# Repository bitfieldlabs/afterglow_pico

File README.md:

# Afterglow Pico
The afterglow pico is the newest and tiniest addition to the afterglow family.

It operates differently from the other boards as it is hooked directly into the WPC bus. The underlying concept remains the same though. The original lamp matrix is resampled at 4kHz and PWM is used to add a nice afterglow to the LEDs in your pinball machine.

## Disclaimer

| :boom: WARNING  :boom:            |
|:---------------------------|
| **Messing with your pinball machine's data bus is risky!** |
| *The AG pico is an experiment, for stable afterglow please<br>use the standard afterglow boards.* |

Afterglow is distributed in the hope that it will be useful but WITHOUT ANY WARRANTY; without even the implied warranty of
MERCHANTABILITY or FITNESS FOR A PARTICULAR PURPOSE.  See the GNU Lesser General Public License for more details.

## Concept
The concept is quite simple:
* The lamp matrix status is sampled directly from the WPC bus by the Raspberry Pi Pico
* All non lamp related address lines (solenoids etc.) are logically combined (AND) to monitor bus activity
* All non lamp related bus events are directly routed through a multiplexer to the output. Only the lamp events are filtered out. This ensures that original bus events always take precedence over the Pi signals and that no original events are lost.
* The Pi Pico interleaves the upsampled 4kHz PWM lamp matrix events into the bus through the multiplexer

## Compiling the Raspberry Pi Pico code

The [pi_pico_code folder](https://github.com/bitfieldlabs/afterglow_pico/tree/master/pi_pico_code) contains a [platformio](https://platformio.org/) project which can be compiled using [Visual Studio Code](https://code.visualstudio.com/). It requires the [wizio-pico](https://github.com/Wiz-IO/wizio-pico) platform extension.

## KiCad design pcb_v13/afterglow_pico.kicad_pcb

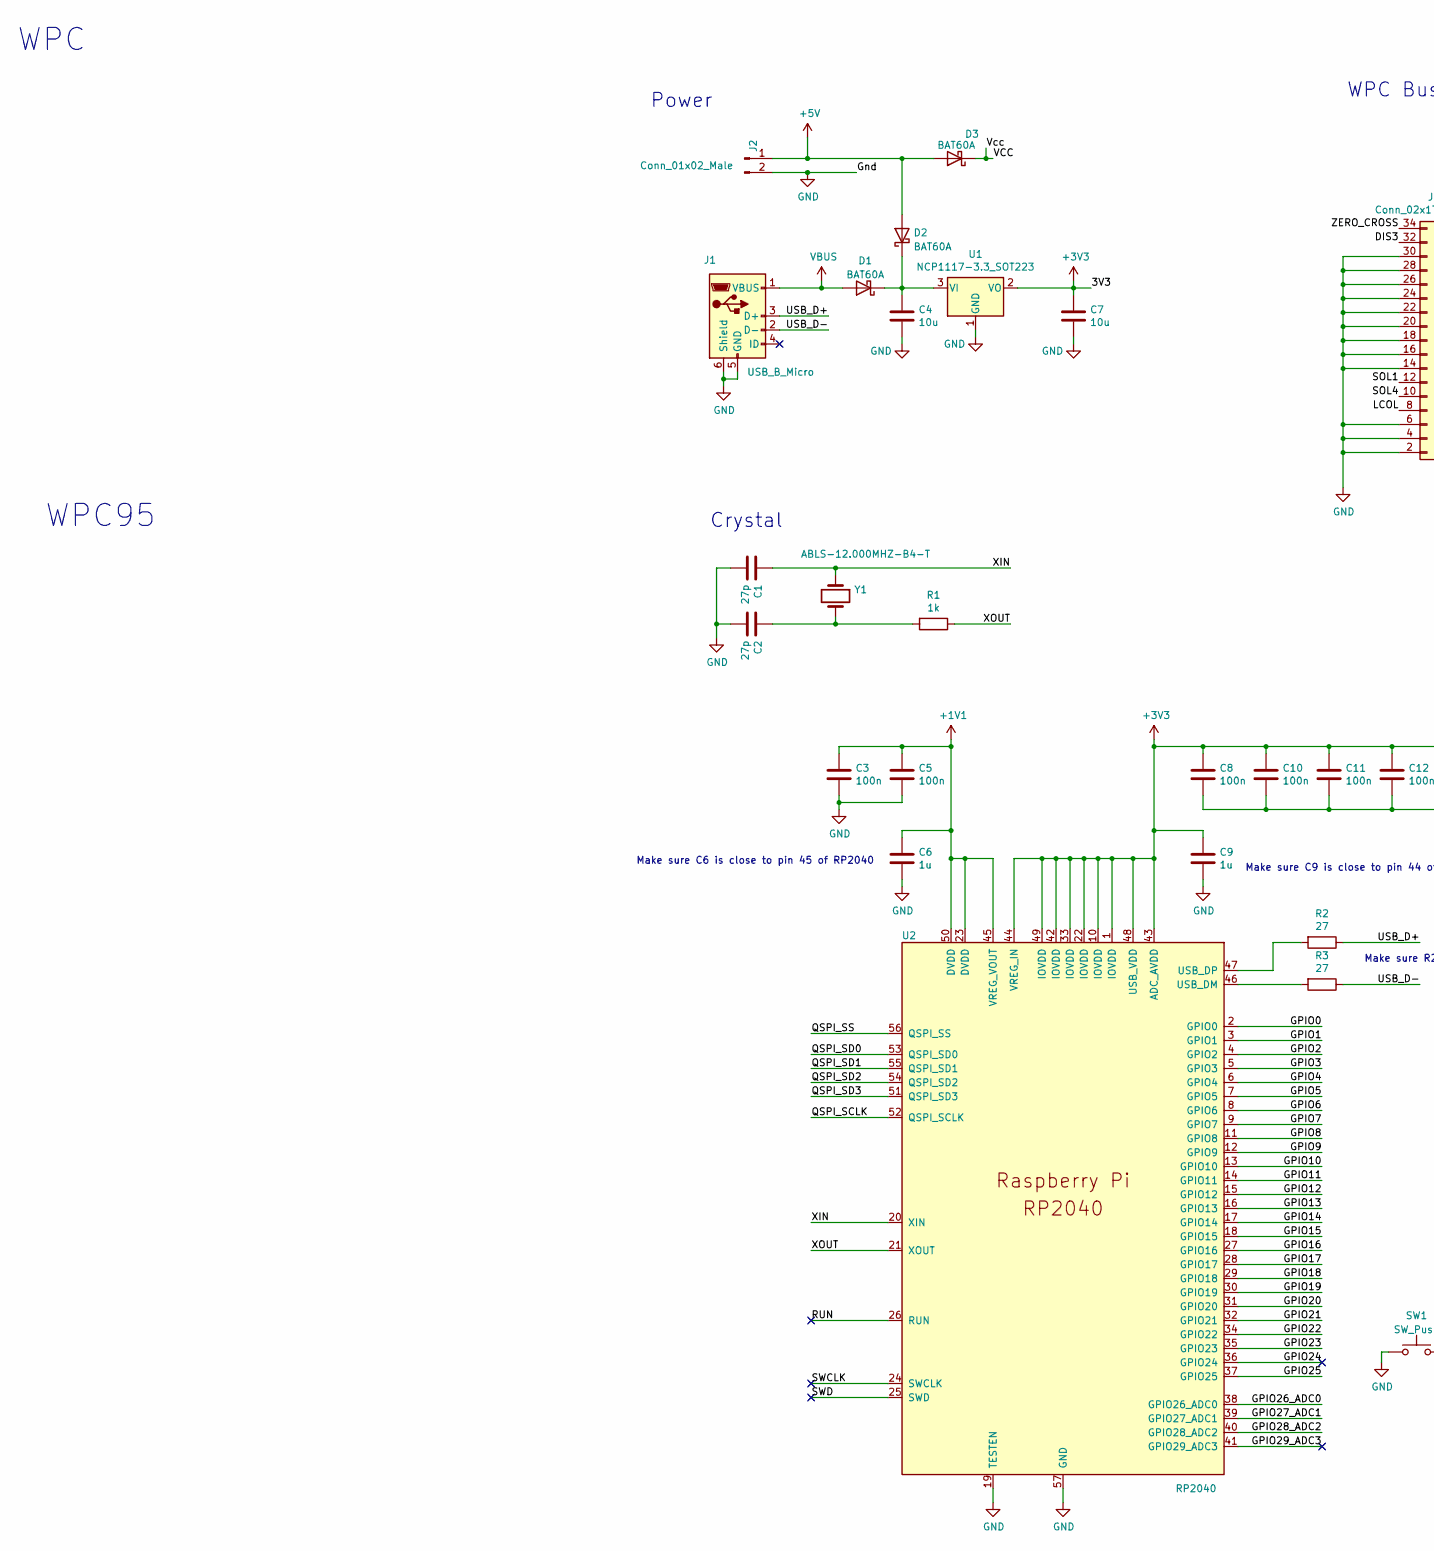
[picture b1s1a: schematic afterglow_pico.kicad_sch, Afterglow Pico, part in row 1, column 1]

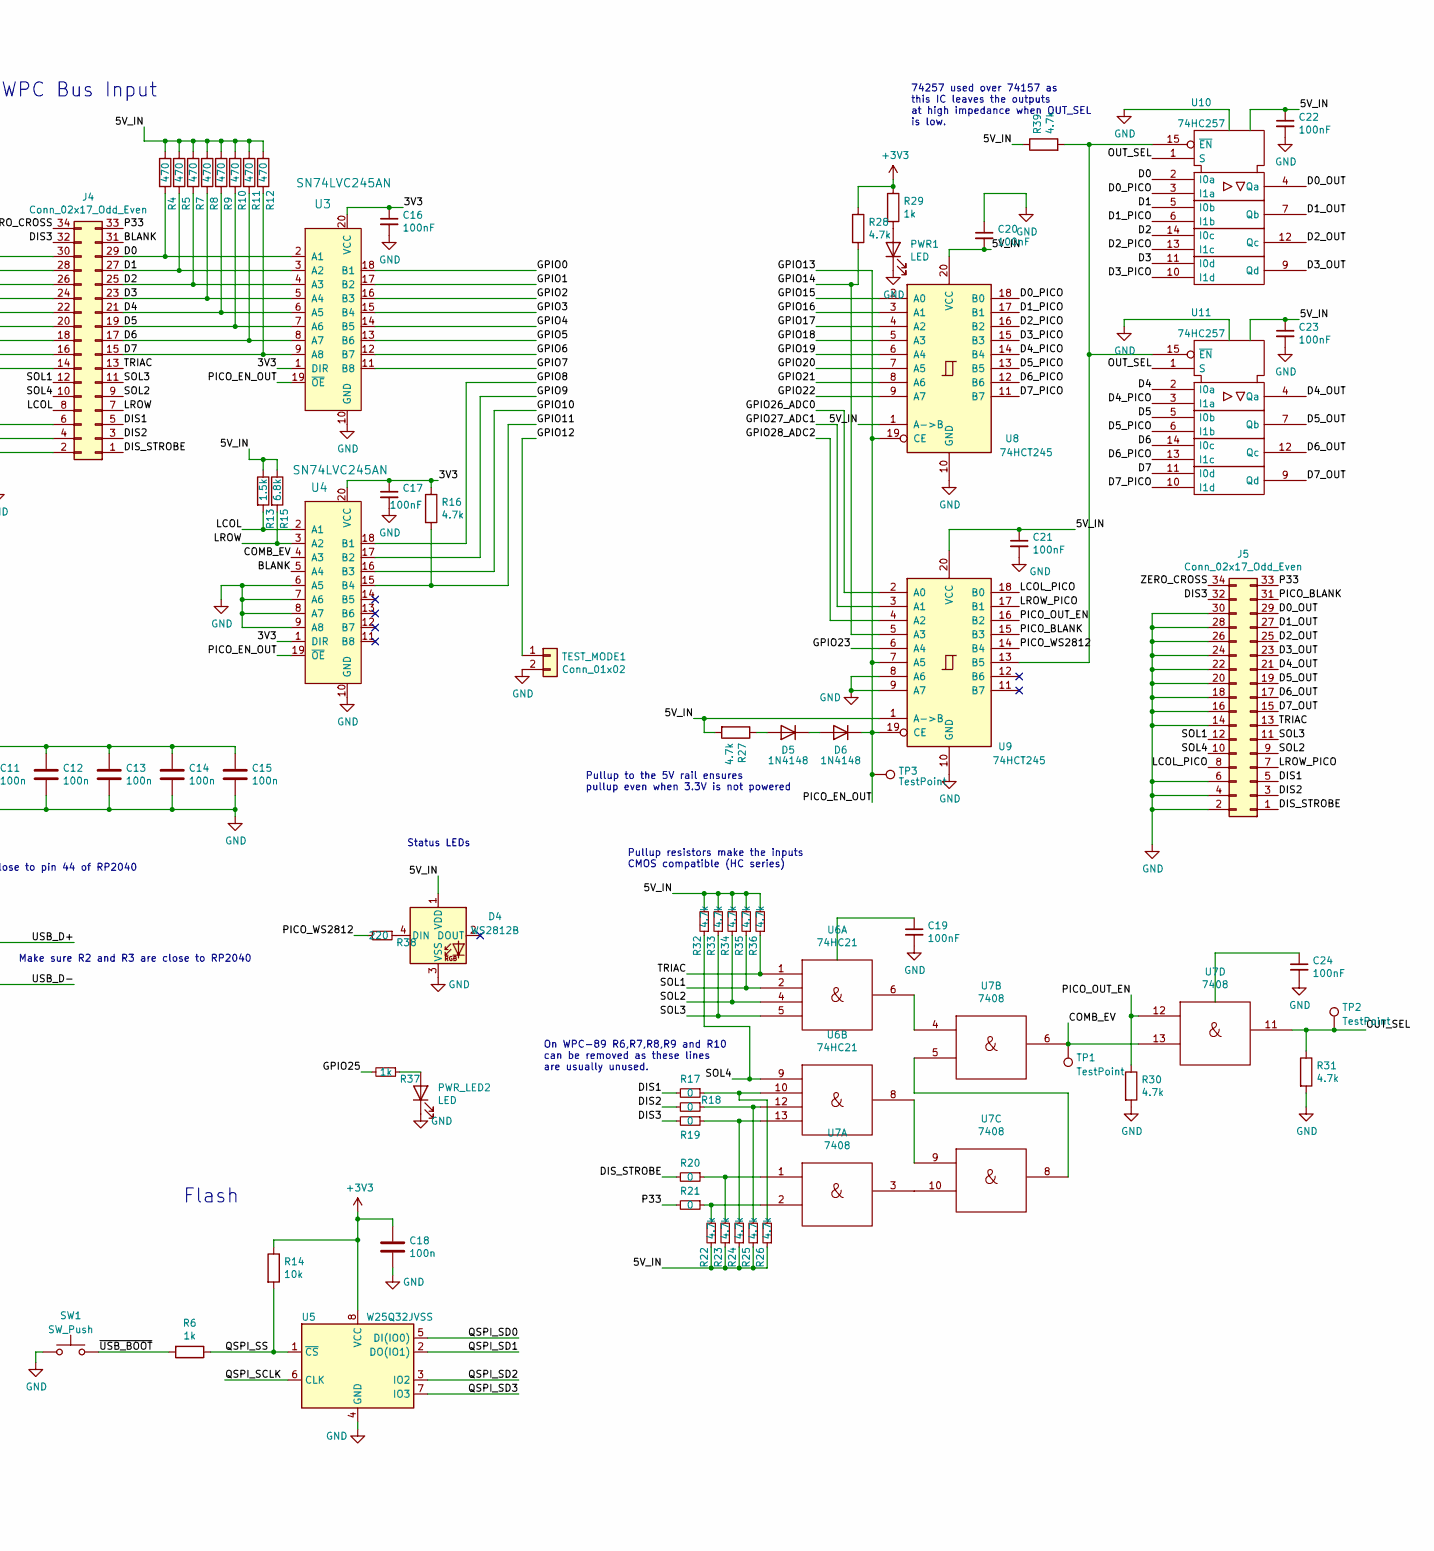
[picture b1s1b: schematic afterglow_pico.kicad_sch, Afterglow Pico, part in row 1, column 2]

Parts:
C1, C2: 27p; C_0402_1005Metric; JLCPCB C107002
C3, C5, C8, C10, C11, C12, C13, C14, C15, C18: 100n; C_0402_1005Metric; JLCPCB C131394
C4, C7: 10u; C_0805_2012Metric; JLCPCB C89189
C6, C9: 1u; C_0402_1005Metric; JLCPCB C326568
C16, C17, C19, C20, C21, C22, C23, C24: 100nF; C_0402_1005Metric; JLCPCB C131394
D1, D2, D3: BAT60A; D_SOD-323; JLCPCB C520634
D4: WS2812B; LED_WS2812B_PLCC4_5.0x5.0mm_P3.2mm; JLCPCB C2761795
D5, D6: 1N4148; D_SOD-523; JLCPCB C2961218
J1: USB_B_Micro; USB_Micro-B_Molex-105017-0001; JLCPCB C505111
J2: Conn_01x02_Male; Molex_KK-254_AE-6410-02A_1x02_P2.54mm_Vertical
J4: Conn_02x17_Odd_Even; PinHeader_2x17_P2.54mm_Vertical
J5: Conn_02x17_Odd_Even; PinHeader_2x17_P2.54mm_Vertical; JLCPCB C2894978
PWR1: LED; LED_0402_1005Metric; JLCPCB C434449
PWR_LED2: LED; LED_0402_1005Metric; JLCPCB C130719
R1, R6, R29, R37: 1k; R_0402_1005Metric; JLCPCB C106235
R2, R3: 27; R_0402_1005Metric; JLCPCB C137890
R4, R5, R7, R8, R9, R10, R11, R12: 470; R_0402_1005Metric; JLCPCB C114877
R13: 1.5k; R_0402_1005Metric; JLCPCB C114759
R14: 10k; R_0402_1005Metric; JLCPCB C60489
R15: 6.8k; R_0402_1005Metric; JLCPCB C137847
R16, R22, R23, R24, R25, R26, R27, R28, R30, R31, R32, R33, R34, R35, R36, R39: 4.7k; R_0402_1005Metric; JLCPCB C105871
R17, R18, R20, R21: 0; R_0402_1005Metric
R19: 0; R_0402_1005Metric; JLCPCB C138289
R38: 220; R_0402_1005Metric; JLCPCB C227335
SW1: SW_Push; SW_SPST_B3U-1000P; JLCPCB C231329
TEST_MODE1: Conn_01x02; PinHeader_1x02_P2.54mm_Vertical; JLCPCB C124375
TP1, TP2, TP3: TestPoint; TestPoint_Pad_D1.5mm
U1: NCP1117-3.3_SOT223; SOT-223-3_TabPin2; JLCPCB C26537
U2: RP2040; RP2040-QFN-56; JLCPCB C2040
U3, U4: SN74LVC245AN; TSSOP-20_4.4x6.5mm_P0.65mm; MPN SN74LVC245AN; Digi-Key_PN 296-8503-5-ND
U5: W25Q32JVSS; SOIC-8_5.23x5.23mm_P1.27mm; JLCPCB C82344
U6: 74HC21; SOIC-14_3.9x8.7mm_P1.27mm; JLCPCB C75398
U7: 7408; SOIC-14_3.9x8.7mm_P1.27mm; JLCPCB C5593
U8, U9: 74HCT245; TSSOP-20_4.4x6.5mm_P0.65mm; JLCPCB C6779
U10, U11: 74HC257; TSSOP-16_4.4x5mm_P0.65mm; JLCPCB C7646
Y1: ABLS-12.000MHZ-B4-T; Crystal_SMD_HC49-US; JLCPCB C390753

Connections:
+1V1: C3.1, C5.1, C6.1, U2.23 (DVDD), U2.45 (VREG_VOUT), U2.50 (DVDD)
+3V3: C7.1, C8.1, C9.1, C10.1, C11.1, C12.1, C13.1, C14.1, C15.1, C16.1, C17.1, C18.1, R14.1, R16.1, R28.1, R29.1, U1.2 (VO), U2.1 (IOVDD), U2.10 (IOVDD), U2.22 (IOVDD), U2.33 (IOVDD), U2.42 (IOVDD), U2.43 (ADC_AVDD), U2.44 (VREG_IN), U2.48 (USB_VDD), U2.49 (IOVDD), U3.1 (DIR), U3.20 (VCC), U4.1 (DIR), U4.20 (VCC), U5.8 (VCC)
+5V: D2.2 (A), D3.2 (A), J2.1; also elsewhere on the board
/BLANK: J4.31, U4.5 (A4)
/COMB_EV: TP1.1, U4.4 (A3), U7.6, U7.13
/D0: J4.29, R4.2, U3.2 (A1), U10.2 (I0a)
/D0_OUT: J5.29, U10.4 (Qa)
/D0_PICO: U8.18 (B0), U10.3 (I1a)
/D1: J4.27, R5.2, U3.3 (A2), U10.5 (I0b)
/D1_OUT: J5.27, U10.7 (Qb)
/D1_PICO: U8.17 (B1), U10.6 (I1b)
/D2: J4.25, R7.2, U3.4 (A3), U10.14 (I0c)
/D2_OUT: J5.25, U10.12 (Qc)
/D2_PICO: U8.16 (B2), U10.13 (I1c)
/D3: J4.23, R8.2, U3.5 (A4), U10.11 (I0d)
/D3_OUT: J5.23, U10.9 (Qd)
/D3_PICO: U8.15 (B3), U10.10 (I1d)
/D4: J4.21, R9.2, U3.6 (A5), U11.2 (I0a)
/D4_OUT: J5.21, U11.4 (Qa)
/D4_PICO: U8.14 (B4), U11.3 (I1a)
/D5: J4.19, R10.2, U3.7 (A6), U11.5 (I0b)
/D5_OUT: J5.19, U11.7 (Qb)
/D5_PICO: U8.13 (B5), U11.6 (I1b)
/D6: J4.17, R11.2, U3.8 (A7), U11.14 (I0c)
/D6_OUT: J5.17, U11.12 (Qc)
/D6_PICO: U8.12 (B6), U11.13 (I1c)
/D7: J4.15, R12.2, U3.9 (A8), U11.11 (I0d)
/D7_OUT: J5.15, U11.9 (Qd)
/D7_PICO: U8.11 (B7), U11.10 (I1d)
/DIS1: J4.5, J5.5, R17.2
/DIS2: J4.3, J5.3, R18.2
/DIS3: J4.32, J5.32, R19.2
/DIS_STROBE: J4.1, J5.1, R20.2
/GPIO0: U2.2 (GPIO0), U3.18 (B1)
/GPIO1: U2.3 (GPIO1), U3.17 (B2)
/GPIO2: U2.4 (GPIO2), U3.16 (B3)
/GPIO3: U2.5 (GPIO3), U3.15 (B4)
/GPIO4: U2.6 (GPIO4), U3.14 (B5)
/GPIO5: U2.7 (GPIO5), U3.13 (B6)
/GPIO6: U2.8 (GPIO6), U3.12 (B7)
/GPIO7: U2.9 (GPIO7), U3.11 (B8)
/GPIO8: U2.11 (GPIO8), U4.18 (B1)
/GPIO9: U2.12 (GPIO9), U4.17 (B2)
/GPIO10: U2.13 (GPIO10), U4.16 (B3)
/GPIO11: R16.2, U2.14 (GPIO11), U4.15 (B4)
/GPIO12: TEST_MODE1.1, U2.15 (GPIO12); also elsewhere on the board
/GPIO13: D6.1 (K), TP3.1, U2.16 (GPIO13), U3.19 (~OE), U4.19 (~OE), U8.19 (CE), U9.7 (A5), U9.19 (CE)
/GPIO14: R28.2, U2.17 (GPIO14), U9.5 (A3)
/GPIO15: U2.18 (GPIO15), U8.2 (A0)
/GPIO16: U2.27 (GPIO16), U8.3 (A1)
/GPIO17: U2.28 (GPIO17), U8.4 (A2)
/GPIO18: U2.29 (GPIO18), U8.5 (A3)
/GPIO19: U2.30 (GPIO19), U8.6 (A4)
/GPIO20: U2.31 (GPIO20), U8.7 (A5)
/GPIO21: U2.32 (GPIO21), U8.8 (A6)
/GPIO22: U2.34 (GPIO22), U8.9 (A7)
/GPIO23: U2.35 (GPIO23), U9.6 (A4)
/GPIO24: U2.36 (GPIO24)
/GPIO25: R37.2, U2.37 (GPIO25)
/GPIO26_ADC0: U2.38 (GPIO26_ADC0), U9.2 (A0)
/GPIO27_ADC1: U2.39 (GPIO27_ADC1), U9.3 (A1)
/GPIO28_ADC2: U2.40 (GPIO28_ADC2), U9.4 (A2)
/GPIO29_ADC3: U2.41 (GPIO29_ADC3)
/LCOL: J4.8, R13.2, U4.2 (A1)
/LCOL_PICO: J5.8, U9.18 (B0)
/LROW: J4.7, R15.2, U4.3 (A2)
/LROW_PICO: J5.7, U9.17 (B1)
/OUT_SEL: R31.1, TP2.1, U7.11, U10.1 (S), U11.1 (S)
/P33: J4.33, J5.33, R21.2
/PICO_BLANK: J5.31, U9.15 (B3)
/PICO_OUT_EN: R30.1, U7.12, U9.16 (B2)
/PICO_WS2812: R38.2, U9.14 (B4)
/QSPI_SCLK: U2.52 (QSPI_SCLK), U5.6 (CLK)
/QSPI_SD0: U2.53 (QSPI_SD0), U5.5 (DI(IO0))
/QSPI_SD1: U2.55 (QSPI_SD1), U5.2 (DO(IO1))
/QSPI_SD2: U2.54 (QSPI_SD2), U5.3 (IO2)
/QSPI_SD3: U2.51 (QSPI_SD3), U5.7 (IO3)
/QSPI_SS: R6.1, R14.2, U2.56 (QSPI_SS), U5.1 (~CS)
/RUN: U2.26 (RUN)
/SOL1: J4.12, J5.12, R35.1, U6.2
/SOL2: J4.9, J5.9, R34.1, U6.4
/SOL3: J4.11, J5.11, R33.1, U6.5
/SOL4: J4.10, J5.10, R32.1, U6.9
/SWCLK: U2.24 (SWCLK)
/SWD: U2.25 (SWD)
/TRIAC: J4.13, J5.13, R36.1, U6.1
/USB_D+: J1.3 (D+), R2.1
/USB_D-: J1.2 (D-), R3.1
/XIN: C1.1, U2.20 (XIN), Y1.1
/XOUT: R1.1, U2.21 (XOUT)
/ZERO_CROSS: J4.34, J5.34
/~USB_BOOT: R6.2, SW1.2
GND: C1.2, C2.2, C3.2, C4.2, C5.2, C6.2, C7.2, C8.2, C9.2, C10.2, C11.2, C12.2, C13.2, C14.2, C15.2, C16.2, C17.2, C18.2, C19.2, C20.1, C21.2, C22.2, C23.2, C24.2, D4.3 (VSS), J1.5 (GND), J1.6 (Shield), J2.2, J4.2, J4.4, J4.6, J4.14, J4.16, J4.18, J4.20, J4.22, J4.24, J4.26, J4.28, J4.30, J5.2, J5.4, J5.6, J5.14, J5.16, J5.18, J5.20, J5.22, J5.24, J5.26, J5.28, J5.30, PWR1.1 (K), PWR_LED2.1 (K), R30.2, R31.2, SW1.1, TEST_MODE1.2, U1.1 (GND), U2.19 (TESTEN), U2.57 (GND), U3.10 (GND), U4.6 (A5), U4.7 (A6), U4.8 (A7), U4.9 (A8), U4.10 (GND), U5.4 (GND), U6.7 (Gnd), U7.7 (Gnd), U8.10 (GND), U9.8 (A6), U9.9 (A7), U9.10 (GND), U10.8 (GND), U11.8 (GND); also elsewhere on the board
unnamed: C2.1, R1.2, Y1.2
unnamed: C4.1, D1.1 (K), D2.1 (K), U1.3 (VI)
unnamed: D4.4 (DIN), R38.1
unnamed: D5.2 (A), R27.1
unnamed: D5.1 (K), D6.2 (A)
unnamed 98: PWR1.2 (A), R29.2; also elsewhere on the board
unnamed: PWR_LED2.2 (A), R37.1
unnamed: R17.1, R26.2, U6.10
unnamed: R18.1, R25.2, U6.12
unnamed: R19.1, R24.2, U6.13
unnamed: R20.1, R23.2, U7.1
unnamed: R21.1, R22.2, U7.2
unnamed: R3.2, U2.46 (USB_DM)
unnamed: R2.2, U2.47 (USB_DP)
unnamed: U6.6, U7.4
unnamed: U6.8, U7.9
unnamed: U7.5, U7.8
unnamed: U7.3, U7.10
unnamed: R39.2, U9.13 (B5), U10.15 (~EN), U11.15 (~EN)
VBUS: D1.2 (A), J1.1 (VBUS)

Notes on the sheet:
WPC
Pullup to the 5V rail ensures pullup even when 3.3V is not powered
Status LEDs
Pullup resistors make the inputs CMOS compatible (HC series)
Make sure C9 is close to pin 44 of RP2040
Power
Crystal
74257 used over 74157 as this IC leaves the outputs at high impedance when OUT_SEL is low.
On WPC-89 R6,R7,R8,R9 and R10 can be removed as these lines are usually unused.
WPC Bus Input
WPC95
Make sure R2 and R3 are close to RP2040
Flash
Make sure C6 is close to pin 45 of RP2040

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
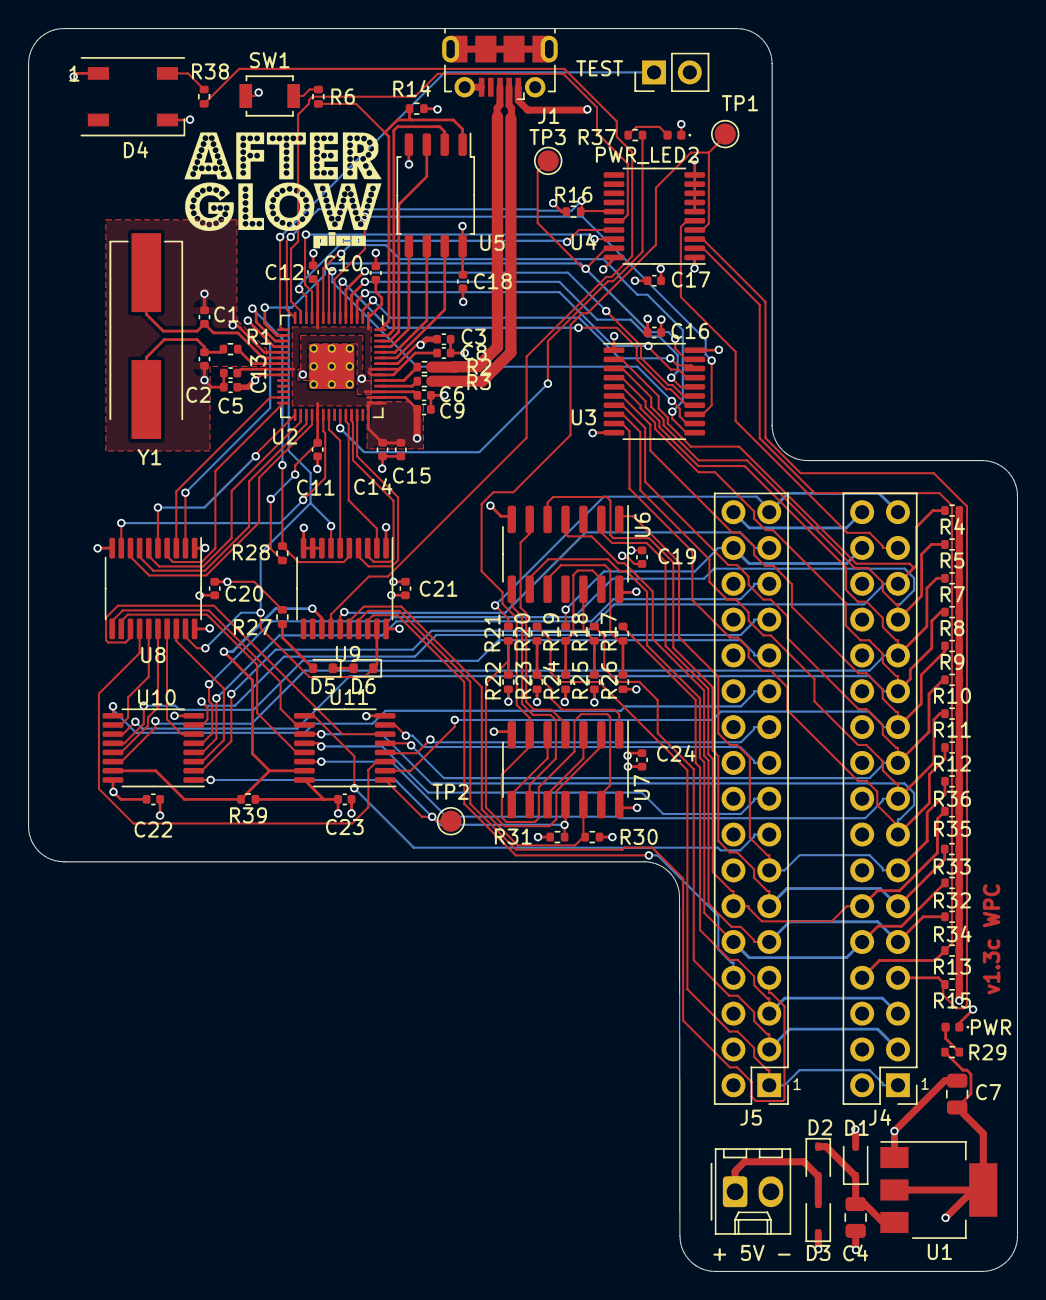
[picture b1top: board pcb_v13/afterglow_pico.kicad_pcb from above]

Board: 4 copper layers, 70.1 x 88.1 mm, 93 parts (0 on the bottom side), 109 nets.

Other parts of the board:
+ 5V -: Conn_01x02_Male; Molex_KK-254_AE-6410-02A_1x02_P2.54mm_Vertical
LOGO: LOGO; ag_pico_logo_2
PWR: LED; LED_0402_1005Metric
TEST: Conn_01x02; PinHeader_1x02_P2.54mm_Vertical

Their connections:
+5V: + 5V -.1; also elsewhere on the board
/GPIO12: TEST.1; also elsewhere on the board
GND: + 5V -.2, PWR.1 (K), TEST.2; also elsewhere on the board
unnamed 98: PWR.2 (A); also elsewhere on the board

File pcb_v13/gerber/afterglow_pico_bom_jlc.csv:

"Comment","Designator","Footprint","LCSC Part #"
"27p","C1,C2","C_0402_1005Metric","C107002"
"100n","C3,C5,C8,C10,C11,C12,C13,C14,C15,C18","C_0402_1005Metric","C131394"
"10u","C4,C7","C_0805_2012Metric","C89189"
"1u","C6,C9","C_0402_1005Metric","C326568"
"100nF","C16,C17,C19,C20,C21,C22,C23,C24","C_0402_1005Metric","C131394"
"BAT60A","D1,D2,D3","D_SOD-323","C520634"
"WS2812B","D4","LED_WS2812B_PLCC4_5.0x5.0mm_P3.2mm","C2761795"
"1N4148","D5,D6","D_SOD-523","C2961218"
"USB_B_Micro","J1","USB_Micro-B_Molex-105017-0001","C505111"
"Conn_02x17_Odd_Even","J5","PinHeader_2x17_P2.54mm_Vertical","C2894978"
"LED","PWR1","LED_0402_1005Metric","C434449"
"LED","PWR_LED2","LED_0402_1005Metric","C130719"
"1k","R1,R6,R29,R37","R_0402_1005Metric","C106235"
"27","R2,R3","R_0402_1005Metric","C137890"
"470","R4,R5,R7,R8,R9,R10,R11,R12","R_0402_1005Metric","C114877"
"1.5k","R13","R_0402_1005Metric","C114759"
"10k","R14","R_0402_1005Metric","C60489"
"6.8k","R15","R_0402_1005Metric","C137847"
"4.7k","R16,R22,R23,R24,R25,R26,R27,R28,R30,R31,R32,R33,R34,R35,R36,R39","R_0402_1005Metric","C105871"
"0","R19","R_0402_1005Metric","C138289"
"220","R38","R_0402_1005Metric","C227335"
"SW_Push","SW1","SW_SPST_B3U-1000P","C231329"
"Conn_01x02","TEST_MODE1","PinHeader_1x02_P2.54mm_Vertical","C124375"
"NCP1117-3.3_SOT223","U1","SOT-223-3_TabPin2","C26537"
"RP2040","U2","RP2040-QFN-56","C2040"
"SN74LVC245AN","U3,U4","TSSOP-20_4.4x6.5mm_P0.65mm","C6082"
"W25Q32JVSS","U5","SOIC-8_5.23x5.23mm_P1.27mm","C82344"
"74HC21","U6","SOIC-14_3.9x8.7mm_P1.27mm","C75398"
"7408","U7","SOIC-14_3.9x8.7mm_P1.27mm","C5593"
"74HCT245","U8,U9","TSSOP-20_4.4x6.5mm_P0.65mm","C6779"
"74HC257","U10,U11","TSSOP-16_4.4x5mm_P0.65mm","C7646"
"ABLS-12.000MHZ-B4-T","Y1","Crystal_SMD_HC49-US","C390753"

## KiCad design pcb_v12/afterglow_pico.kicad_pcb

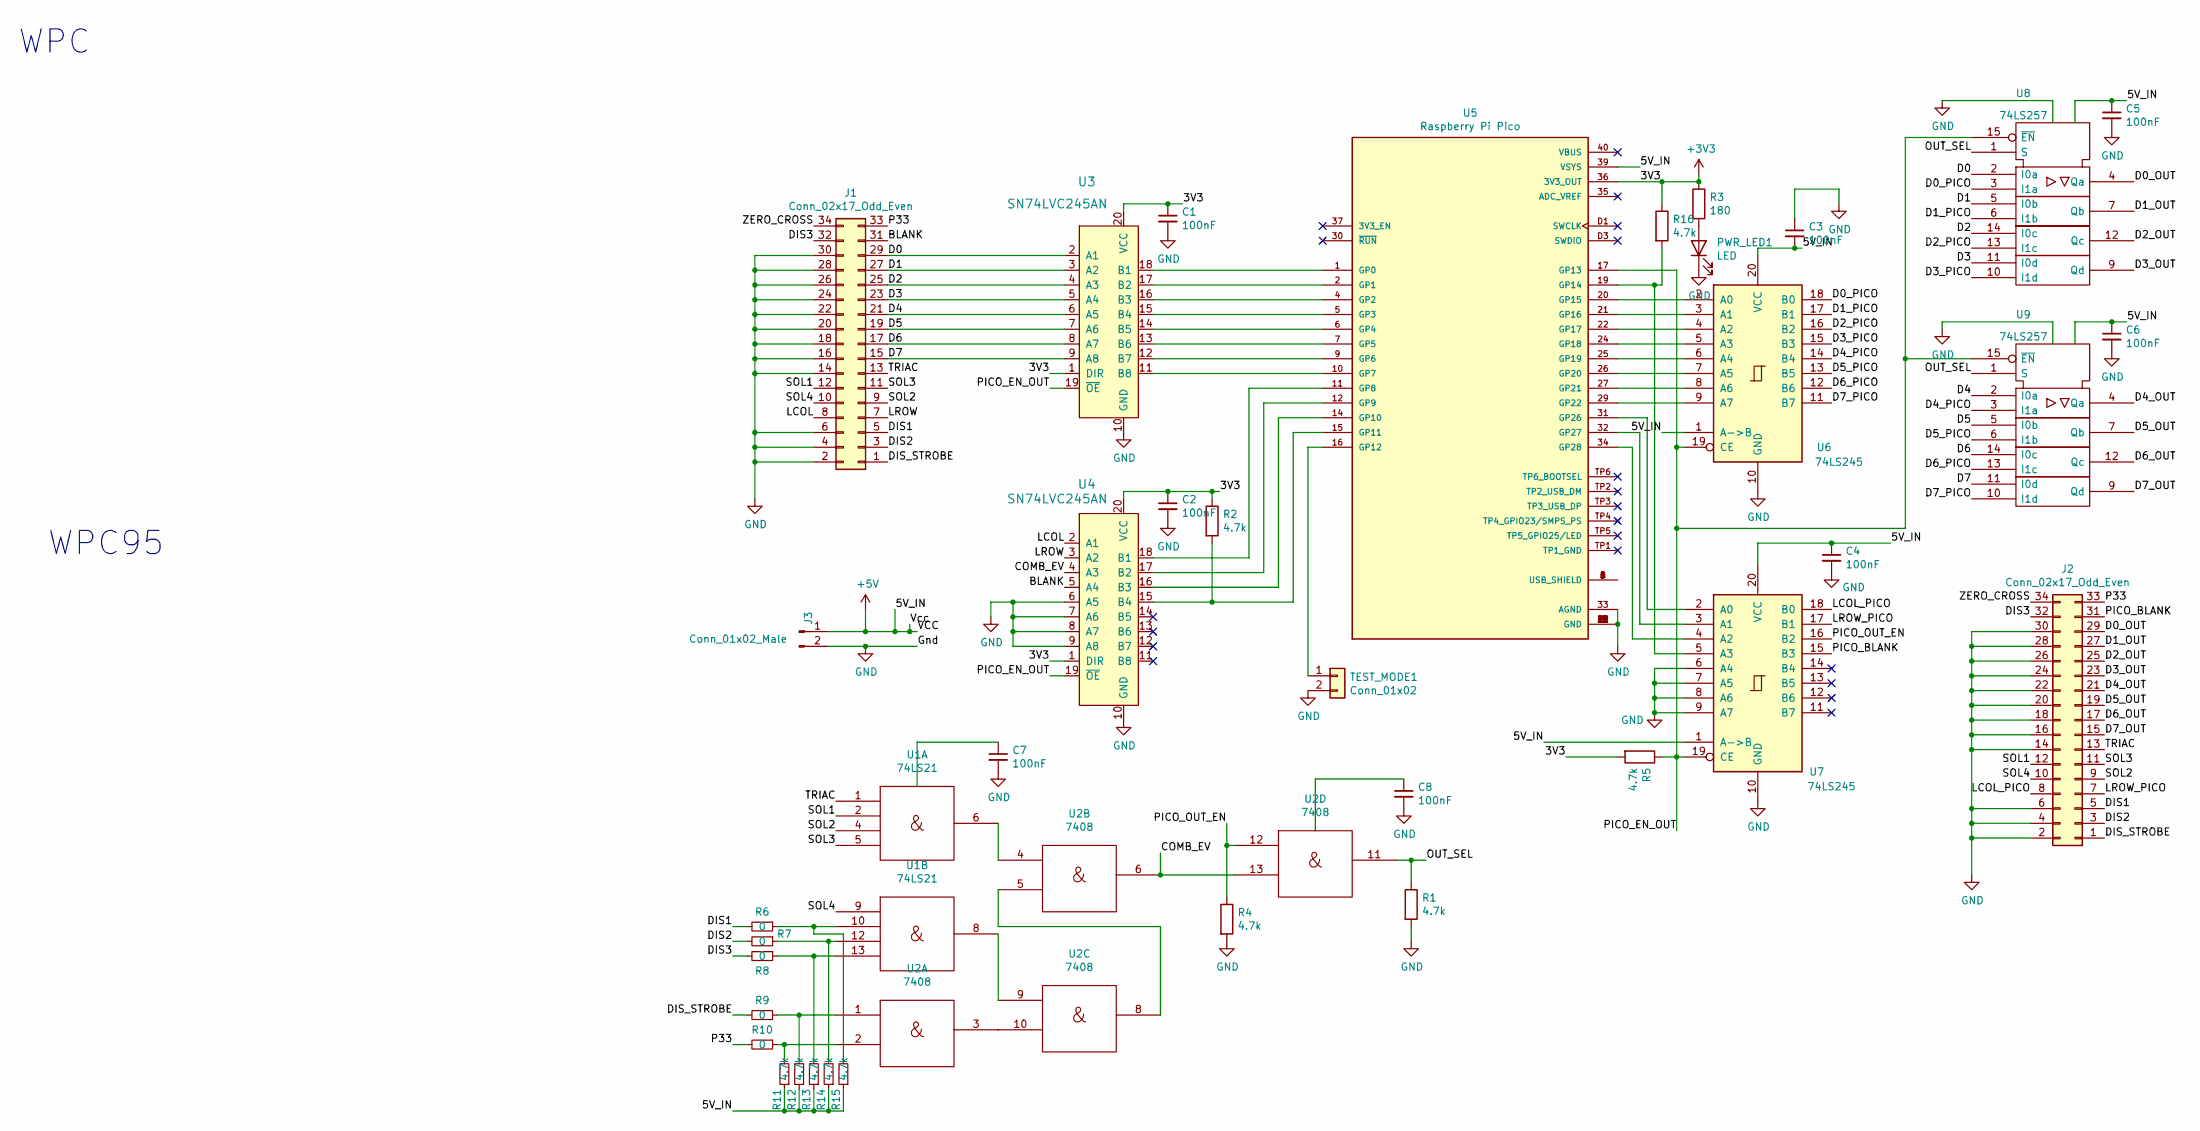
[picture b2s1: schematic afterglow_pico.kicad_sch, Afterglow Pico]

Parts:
C1, C2, C3, C4, C5, C6, C7, C8: 100nF; C_0805_HandSoldering; JLCPCB C396718
J1, J2: Conn_02x17_Odd_Even; Pin_Header_Straight_2x17_Pitch2.54mm
J3: Conn_01x02_Male; Molex_KK-6410-02_02x2.54mm_Straight
PWR_LED1: LED; LED_0805_HandSoldering; JLCPCB C434432
R1, R2, R4, R5, R11, R12, R13, R14, R15, R16: 4.7k; R_0805_HandSoldering; JLCPCB C17673
R3: 180; R_0805_HandSoldering; JLCPCB C25270
R6, R7, R8, R9, R10: 0; R_0805_HandSoldering; JLCPCB C17477
TEST_MODE1: Conn_01x02; Pin_Header_Straight_1x02_Pitch2.54mm
U1: 74LS21; SOIC-14_3.9x8.7mm_Pitch1.27mm; JLCPCB C2862597
U2: 7408; SOIC-14_3.9x8.7mm_Pitch1.27mm; JLCPCB C6802
U3, U4: SN74LVC245AN; SOIC-20W_7.5x12.8mm_Pitch1.27mm; MPN SN74LVC245AN; Digi-Key_PN 296-8503-5-ND
U5: Raspberry Pi Pico; MODULE_SC0915; PARTREV 1.6
U6, U7: 74LS245; SOIC-20W_7.5x12.8mm_Pitch1.27mm; JLCPCB C129580
U8, U9: 74LS257; SOP-16_4.4x10.4mm_Pitch1.27mm; JLCPCB C7754

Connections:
+3V3: C1.1, C2.1, R2.1, R3.1, R5.2, R16.1, U3.1 (DIR), U3.20 (VCC), U4.1 (DIR), U4.20 (VCC), U5.36 (3V3_OUT)
/BLANK: J1.31, U4.5 (A4)
/COMB_EV: U2.6, U2.13, U4.4 (A3)
/D0: J1.29, U3.2 (A1), U8.2 (I0a)
/D0_OUT: J2.29, U8.4 (Qa)
/D0_PICO: U6.18 (B0), U8.3 (I1a)
/D1: J1.27, U3.3 (A2), U8.5 (I0b)
/D1_OUT: J2.27, U8.7 (Qb)
/D1_PICO: U6.17 (B1), U8.6 (I1b)
/D2: J1.25, U3.4 (A3), U8.14 (I0c)
/D2_OUT: J2.25, U8.12 (Qc)
/D2_PICO: U6.16 (B2), U8.13 (I1c)
/D3: J1.23, U3.5 (A4), U8.11 (I0d)
/D3_OUT: J2.23, U8.9 (Qd)
/D3_PICO: U6.15 (B3), U8.10 (I1d)
/D4: J1.21, U3.6 (A5), U9.2 (I0a)
/D4_OUT: J2.21, U9.4 (Qa)
/D4_PICO: U6.14 (B4), U9.3 (I1a)
/D5: J1.19, U3.7 (A6), U9.5 (I0b)
/D5_OUT: J2.19, U9.7 (Qb)
/D5_PICO: U6.13 (B5), U9.6 (I1b)
/D6: J1.17, U3.8 (A7), U9.14 (I0c)
/D6_OUT: J2.17, U9.12 (Qc)
/D6_PICO: U6.12 (B6), U9.13 (I1c)
/D7: J1.15, U3.9 (A8), U9.11 (I0d)
/D7_OUT: J2.15, U9.9 (Qd)
/D7_PICO: U6.11 (B7), U9.10 (I1d)
/DIS1: J1.5, J2.5, R6.2
/DIS2: J1.3, J2.3, R7.2
/DIS3: J1.32, J2.32, R8.2
/DIS_STROBE: J1.1, J2.1, R9.2
/LCOL: J1.8, U4.2 (A1)
/LCOL_PICO: J2.8, U7.18 (B0)
/LROW: J1.7, U4.3 (A2)
/LROW_PICO: J2.7, U7.17 (B1)
/OUT_SEL: R1.1, U2.11, U8.1 (S), U9.1 (S)
/P33: J1.33, J2.33, R10.2
/PICO_BLANK: J2.31, U7.15 (B3)
/PICO_EN_OUT: R5.1, U3.19 (~OE), U4.19 (~OE), U5.17 (GP13), U6.19 (CE), U7.19 (CE), U8.15 (~EN), U9.15 (~EN)
/PICO_OUT_EN: R4.1, U2.12, U7.16 (B2)
/SOL1: J1.12, J2.12, U1.2
/SOL2: J1.9, J2.9, U1.4
/SOL3: J1.11, J2.11, U1.5
/SOL4: J1.10, J2.10, U1.9
/TRIAC: J1.13, J2.13, U1.1
/ZERO_CROSS: J1.34, J2.34
GND: C1.2, C2.2, C3.1, C4.2, C5.2, C6.2, C7.2, C8.2, J1.2, J1.4, J1.6, J1.14, J1.16, J1.18, J1.20, J1.22, J1.24, J1.26, J1.28, J1.30, J2.2, J2.4, J2.6, J2.14, J2.16, J2.18, J2.20, J2.22, J2.24, J2.26, J2.28, J2.30, J3.2, PWR_LED1.1 (K), R1.2, R4.2, TEST_MODE1.2, U1.7 (Gnd), U2.7 (Gnd), U3.10 (GND), U4.6 (A5), U4.7 (A6), U4.8 (A7), U4.9 (A8), U4.10 (GND), U5.3 (GND), U5.8 (GND), U5.13 (GND), U5.18 (GND), U5.23 (GND), U5.28 (GND), U5.33 (AGND), U5.38 (GND), U5.D2 (GND), U6.10 (GND), U7.6 (A4), U7.7 (A5), U7.8 (A6), U7.9 (A7), U7.10 (GND), U8.8 (GND), U9.8 (GND); also elsewhere on the board
unnamed 47: PWR_LED1.2 (A), R3.2; also elsewhere on the board
unnamed: R2.2, U4.15 (B4), U5.15 (GP11)
unnamed: R10.1, R11.2, U2.2
unnamed: R9.1, R12.2, U2.1
unnamed: R8.1, R13.2, U1.13
unnamed: R7.1, R14.2, U1.12
unnamed: R6.1, R15.2, U1.10
unnamed: R16.2, U5.19 (GP14), U7.5 (A3)
unnamed 55: TEST_MODE1.1, U5.16 (GP12); also elsewhere on the board
unnamed: U1.6, U2.4
unnamed: U1.8, U2.9
unnamed: U2.5, U2.8
unnamed: U2.3, U2.10
unnamed: U3.11 (B8), U5.10 (GP7)
unnamed: U3.12 (B7), U5.9 (GP6)
unnamed: U3.13 (B6), U5.7 (GP5)
unnamed: U3.14 (B5), U5.6 (GP4)
unnamed: U3.15 (B4), U5.5 (GP3)
unnamed: U3.16 (B3), U5.4 (GP2)
unnamed: U3.17 (B2), U5.2 (GP1)
unnamed: U3.18 (B1), U5.1 (GP0)
unnamed: U4.16 (B3), U5.14 (GP10)
unnamed: U4.17 (B2), U5.12 (GP9)
unnamed: U4.18 (B1), U5.11 (GP8)
unnamed: U5.20 (GP15), U6.2 (A0)
unnamed: U5.21 (GP16), U6.3 (A1)
unnamed: U5.22 (GP17), U6.4 (A2)
unnamed: U5.24 (GP18), U6.5 (A3)
unnamed: U5.25 (GP19), U6.6 (A4)
unnamed: U5.26 (GP20), U6.7 (A5)
unnamed: U5.27 (GP21), U6.8 (A6)
unnamed: U5.29 (GP22), U6.9 (A7)
unnamed: U5.31 (GP26), U7.2 (A0)
unnamed: U5.32 (GP27), U7.3 (A1)
unnamed: U5.34 (GP28), U7.4 (A2)
unnamed: U5.A (USB_SHIELD), U5.B (USB_SHIELD), U5.C (USB_SHIELD), U5.D (USB_SHIELD)

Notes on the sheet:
WPC
WPC95

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
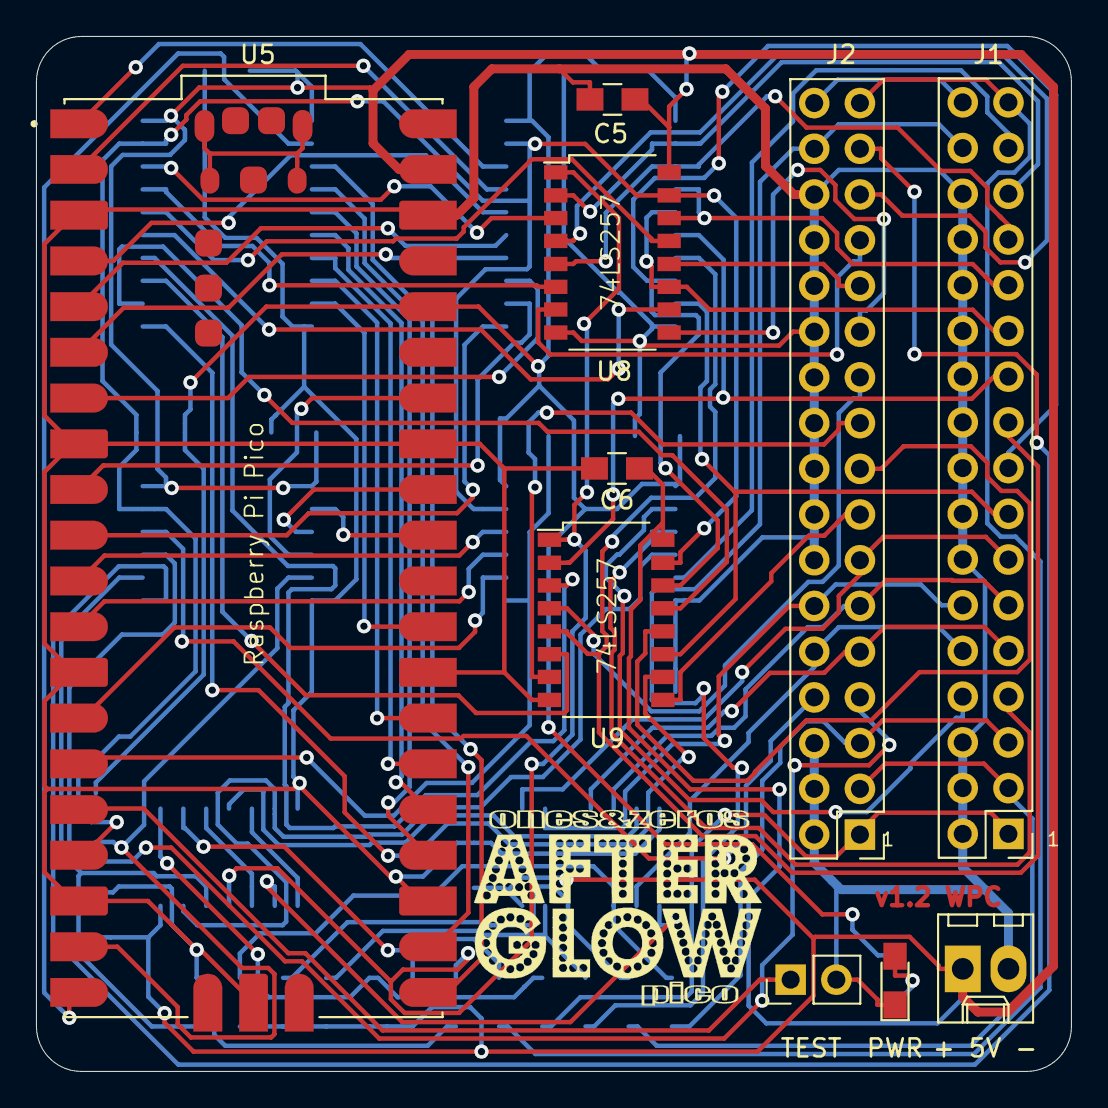
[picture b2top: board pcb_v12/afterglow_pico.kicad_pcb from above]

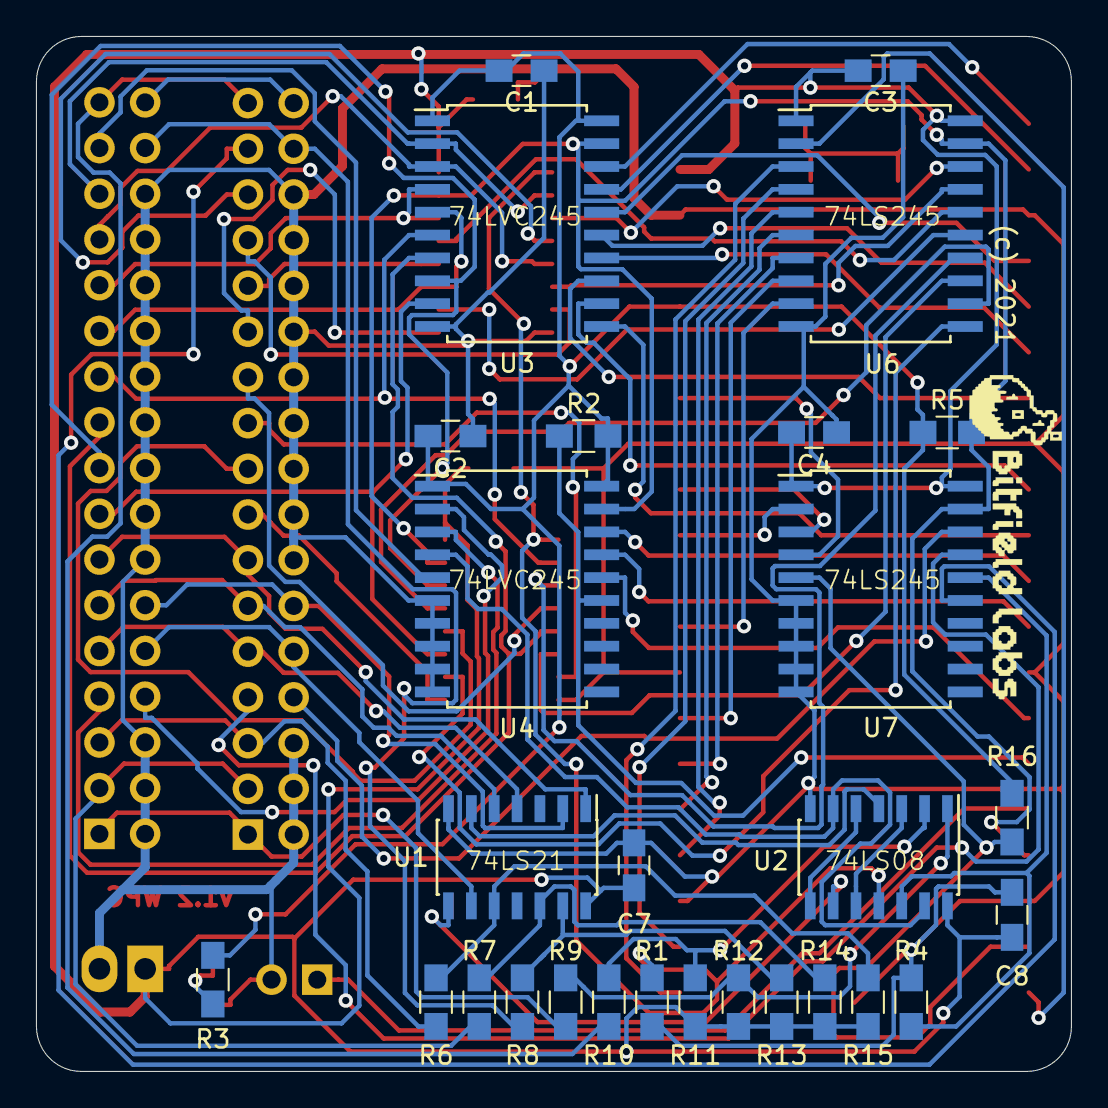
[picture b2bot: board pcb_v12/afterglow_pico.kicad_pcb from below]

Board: 2 copper layers, 57.5 x 57.5 mm, 40 parts (29 on the bottom side), 84 nets.

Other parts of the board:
+ 5V -: Conn_01x02_Male; Molex_KK-6410-02_02x2.54mm_Straight
AG_LOGO: LOGO; ag_pico_logo_2
BFL_LOGO: LOGO; bl_logo
PWR: LED; LED_0805_HandSoldering
TEST: Conn_01x02; Pin_Header_Straight_1x02_Pitch2.54mm

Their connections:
GND: + 5V -.2, PWR.1, TEST.2; also elsewhere on the board
unnamed 47: PWR.2; also elsewhere on the board
unnamed 55: TEST.1; also elsewhere on the board

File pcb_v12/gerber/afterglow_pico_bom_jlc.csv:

"Comment","Designator","Footprint","LCSC Part #"
"100nF","C1,C2,C3,C4,C5,C6,C7,C8","C_0805_HandSoldering","C396718"
"LED","PWR_LED1","LED_0805_HandSoldering","C434432"
"4.7k","R1,R2,R4,R5,R11,R12,R13,R14,R15,R16","R_0805_HandSoldering","C17673"
"180","R3","R_0805_HandSoldering","C25270"
"0","R6,R7,R8,R9,R10","R_0805_HandSoldering","C17477"
"74LS21","U1","SOIC-14_3.9x8.7mm_Pitch1.27mm","C2862597"
"7408","U2","SOIC-14_3.9x8.7mm_Pitch1.27mm","C6802"
"SN74LVC245AN","U3,U4","SOIC-20W_7.5x12.8mm_Pitch1.27mm","C6080"
"74LS245","U6,U7","SOIC-20W_7.5x12.8mm_Pitch1.27mm","C129580"
"74LS257","U8,U9","SOP-16_4.4x10.4mm_Pitch1.27mm","C7754"

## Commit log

2021-12-03 Added schematic pdf
2021-12-03 Added pcb render
2021-12-03 Added v1.1 gerber files
2021-12-03 Some cleanup
2021-12-04 More code cleanup
2021-12-04 Bad blanking fixed
2021-12-11 Improved panicking
2021-12-17 Small robustness improvements
2021-12-19 PCB v1.2 preparations
2021-12-19 PCB v1.2
2021-12-19 Routing preparations
2021-12-19 PCB v1.2 routed
2021-12-19 Fixed url
2021-12-19 Fixed fixed url
2021-12-20 PCB cosmetix
2021-12-25 Schematic cosmetics
2022-01-07 Better GPIO initialisation
2022-03-11 JLCPCB production files
2023-01-01 Improved input handling
2023-01-07 Preparing for PCB v1.3
2023-01-07 Before routing
2023-01-08 First PCB v1.3 draft
2023-01-13 PCB v1.3 progress
2023-01-27 Routable PCB
2023-02-25 First attempt
2023-02-25 Placement
2023-02-25 Power routing
2023-02-25 Boettn
2023-02-26 Almost
2023-02-26 Preparations
2023-02-26 More preparations
2023-02-26 Even more preparations
2023-02-26 Forgot a resistor
2023-02-26 JLCPCB part numbers
2023-02-26 Avoid vias on tracks
2023-02-26 Minor corrections
2023-02-26 PCB v1.3
2023-02-26 Added 3D components
2023-03-10 Keeping project up to date
2023-03-12 PCB v1.3b preparations
2023-03-12 PCB v1.3b
2023-03-12 PCB v1.3b touchup
2023-03-17 Blender render
2023-03-18 Do not populate R17,R18,R20,R21
2023-03-19 PCB v1.3 picture
2023-08-23 ws2812 pio experiment
2023-08-23 WS2812 PIO working
2023-08-23 Attempting to merge upstream changes2
2023-08-23 added some comments
2023-08-23 Added uf2 binary
2023-08-23 cleanup
2023-08-23 Some serial communication
2023-09-14 Restored lost PCB v1.3 schematic
2023-10-08 PCB v1.c fixes track cleareance issues
2023-10-09 PCB v1.3c

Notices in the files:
pcb_v12/afterglow_pico.kicad_pcb:
(c) 2021
